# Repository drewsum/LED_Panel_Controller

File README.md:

# LED_Panel_Controller
Controls a single 64x64 HUB75E LED Panel

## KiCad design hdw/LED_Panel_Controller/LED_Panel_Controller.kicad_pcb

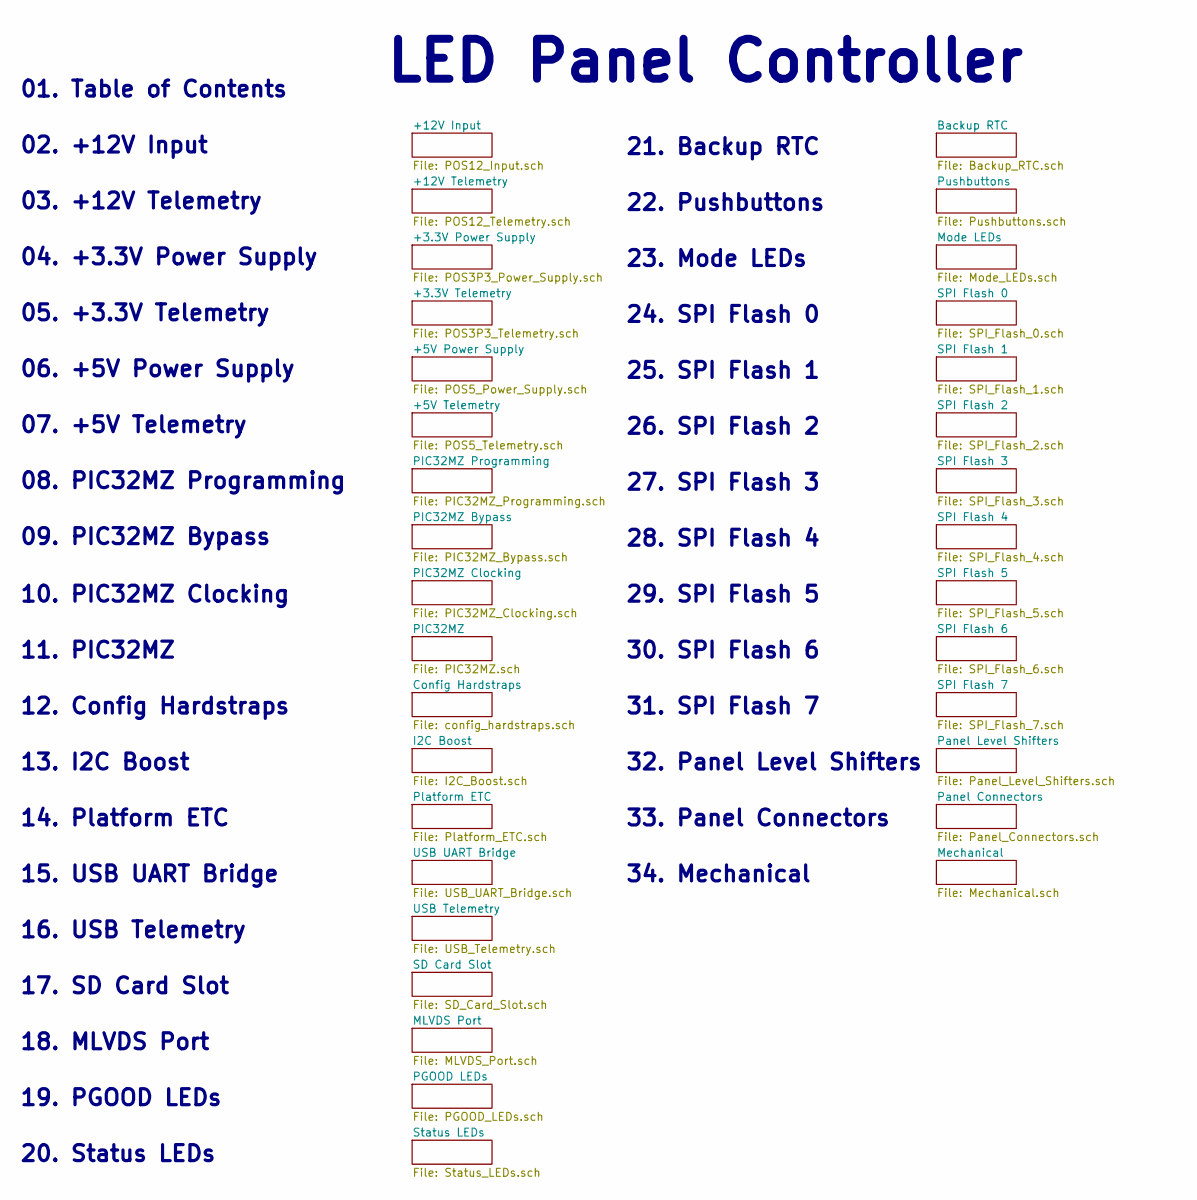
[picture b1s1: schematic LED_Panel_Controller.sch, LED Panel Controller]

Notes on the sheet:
LED Panel Controller
02. +12V Input
03. +12V Telemetry
04. +3.3V Power Supply
05. +3.3V Telemetry
06. +5V Power Supply
07. +5V Telemetry
08. PIC32MZ Programming
09. PIC32MZ Bypass
10. PIC32MZ Clocking
11. PIC32MZ
12. Config Hardstraps
13. I2C Boost
14. Platform ETC
15. USB UART Bridge
17. SD Card Slot
18. MLVDS Port
19. PGOOD LEDs
20. Status LEDs
21. Backup RTC
01. Table of Contents
22. Pushbuttons
23. Mode LEDs
24. SPI Flash 0
25. SPI Flash 1
26. SPI Flash 2
27. SPI Flash 3
28. SPI Flash 4
29. SPI Flash 5
30. SPI Flash 6
31. SPI Flash 7
32. Panel Level Shifters
33. Panel Connectors
34. Mechanical
16. USB Telemetry

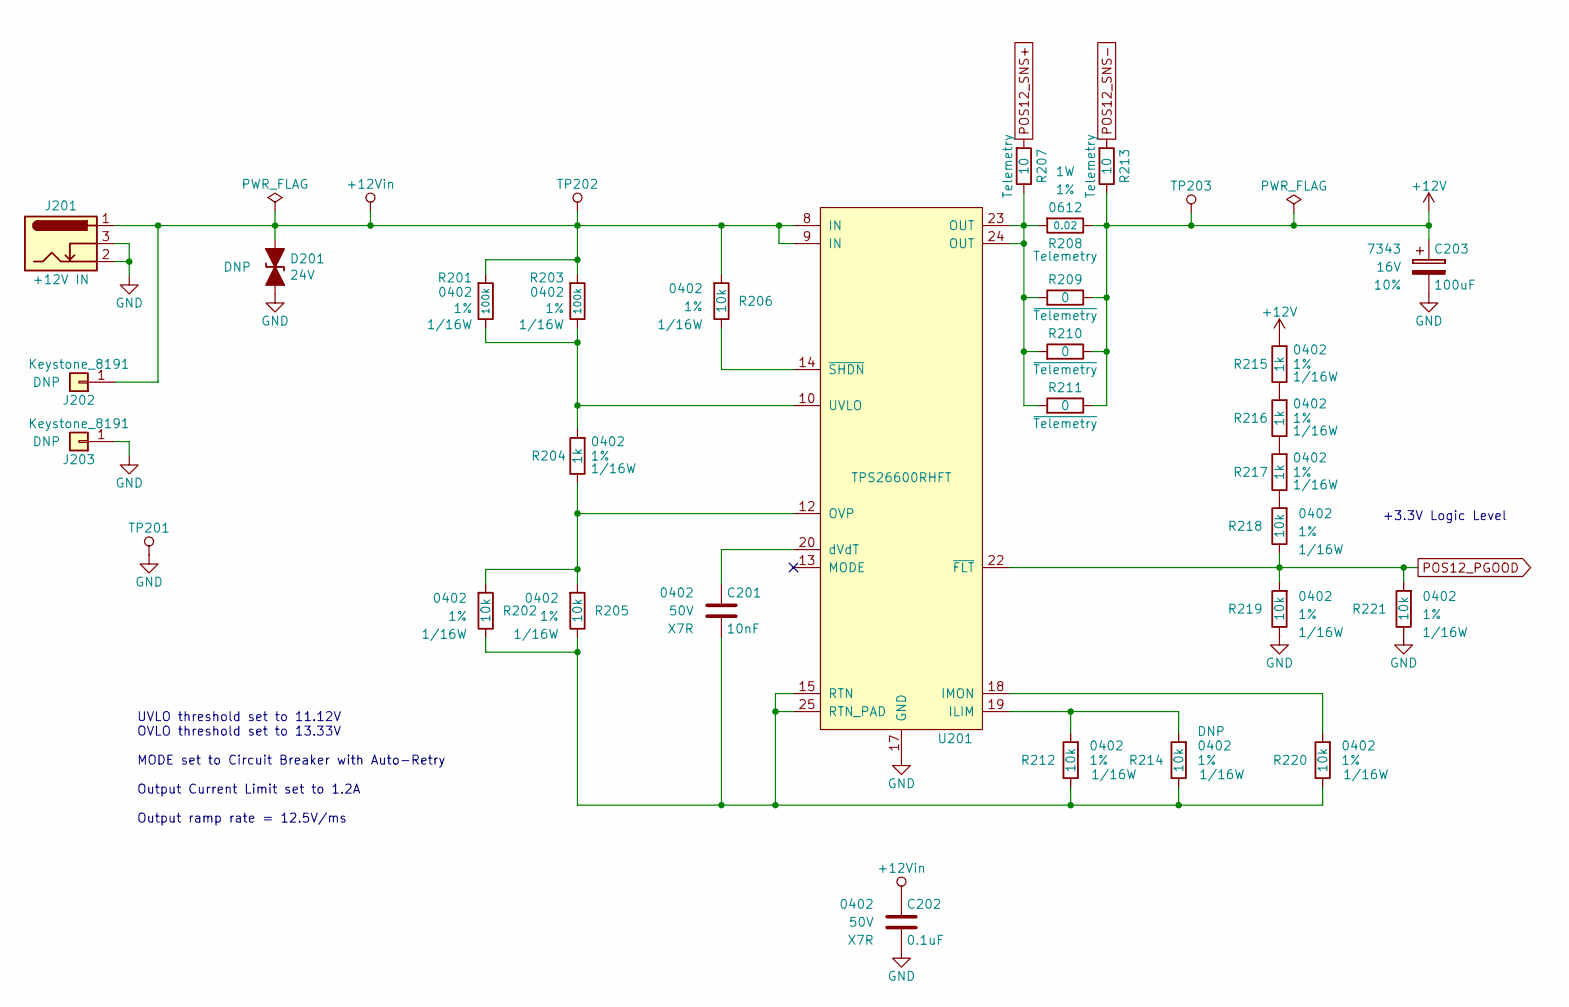
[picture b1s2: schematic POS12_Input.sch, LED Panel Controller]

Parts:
C201: 10nF; C_0402; Voltage 50V; Digi-Key PN 399-3066-1-ND
C202: 0.1uF; C_0402; Voltage 50V; Digi-Key PN 490-10698-1-ND
C203: 100uF; CP_Tantalum_Case-X_EIA-7343-43_Reflow; Voltage 16V; Tolerance 10%; Digi-Key PN 718-1102-1-ND
D201: 24V; D_SMA; Digi-Key PN SMAJ24CALFCT-ND
J201: +12V IN; BARREL_JACK
J202, J203: Keystone_8191; Digi-Key PN 36-8191-ND
R201, R203: 100k; R_0402; Tolerance 1%; Digi-Key PN RMCF0402FT100KCT-ND
R202, R205, R206, R212, R214, R218, R219, R220, R221: 10k; R_0402; Tolerance 1%; Digi-Key PN RMCF0402FT10K0CT-ND
R204, R215, R216, R217: 1k; R_0402; Tolerance 1%; Digi-Key PN RMCF0402FT1K00CT-ND
R207, R213: 10; R_0402; Tolerance 1%; Digi-Key PN RMCF0402FT10R0CT-ND
R208: 0.02; R_0612; Tolerance 1%; Digi-Key PN P16010CT-ND
R209, R210, R211: 0; R_0402; Tolerance 1%; Digi-Key PN RMCF0402ZT0R00CT-ND
TP201: TP; Pin_Header_Angled_1x01_Pitch2.54mm
TP202, TP203: TP; Test_Point
U201: TPS26600RHFT; QFN-24-1EP_4x5mm_Pitch0.5mm; Digi-Key PN 296-45478-1-ND

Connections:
+12V: C203.1, R208.2, R209.2, R210.2, R211.2, R213.2, R215.1, TP203.1; also elsewhere on the board
+12Vin: C202.1, D201.1 (A1), J201.1, J202.1, R201.1, R203.1, R206.1, TP202.1, U201.8 (IN), U201.9 (IN)
unnamed: C201.1, U201.20 (dVdT)
unnamed: C201.2, R202.2, R205.2, R212.2, R214.2, R220.2, U201.15 (RTN), U201.25 (RTN_PAD)
unnamed: R201.2, R203.2, R204.1, U201.10 (UVLO)
unnamed: R202.1, R204.2, R205.1, U201.12 (OVP)
unnamed: R206.2, U201.14 (~SHDN)
unnamed: R207.2, R208.1, R209.1, R210.1, R211.1, U201.23 (OUT), U201.24 (OUT)
unnamed: R212.1, R214.1, U201.19 (ILIM)
unnamed: R215.2, R216.1
unnamed: R216.2, R217.1
unnamed: R217.2, R218.1
unnamed: R220.1, U201.18 (IMON)
POS12_PGOOD: R218.2, R219.1, R221.1, U201.22 (~FLT); also elsewhere on the board
POS12_SNS+: R207.1; also elsewhere on the board
POS12_SNS-: R213.1; also elsewhere on the board

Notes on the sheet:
UVLO threshold set to 11.12V OVLO threshold set to 13.33V MODE set to Circuit Breaker with Auto-Retry Output Current Limit set to 1.2A Output ramp rate = 12.5V/ms
+3.3V Logic Level

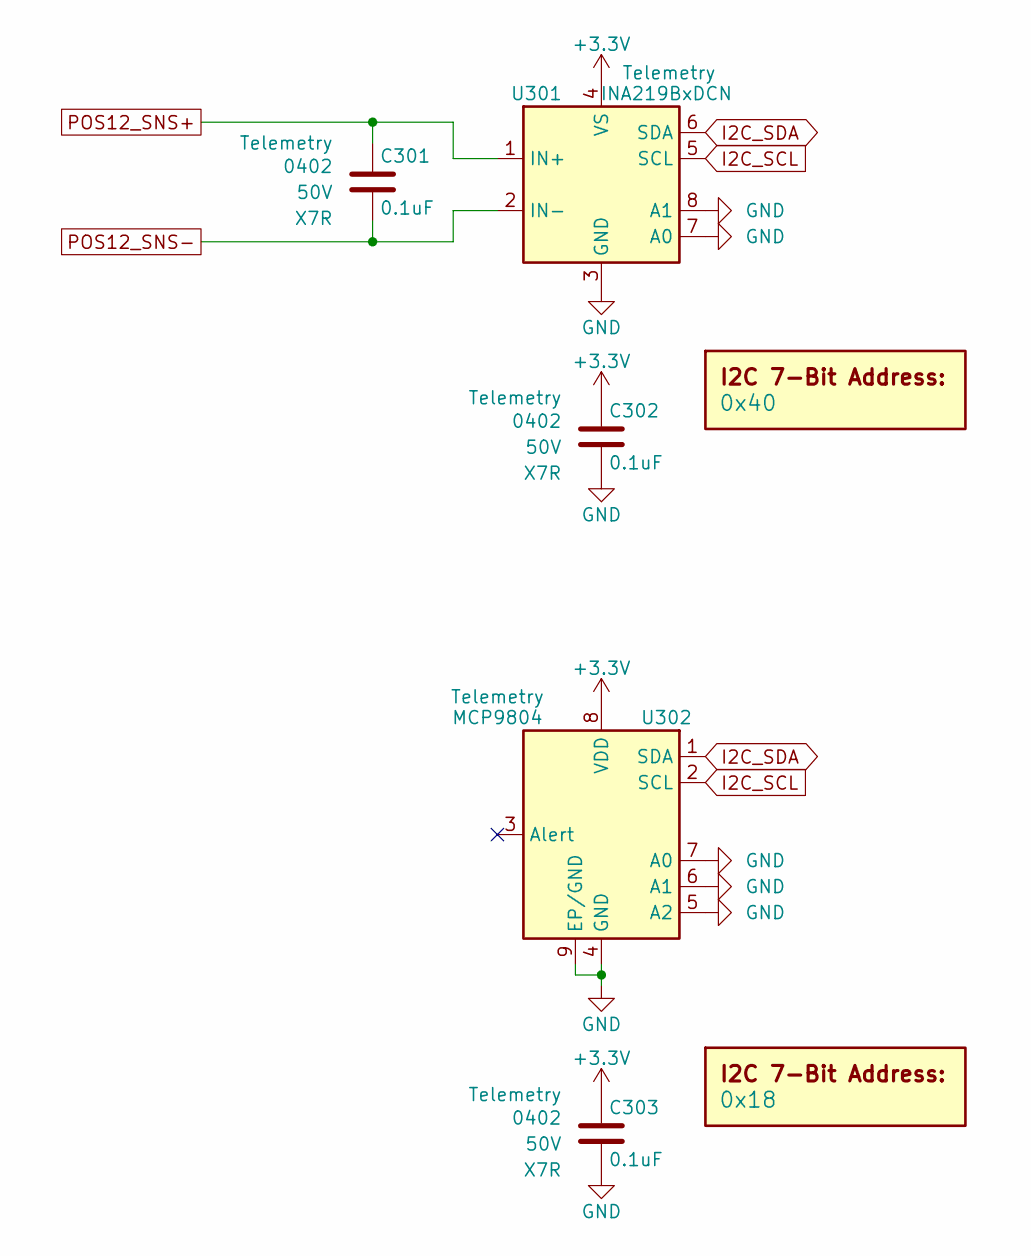
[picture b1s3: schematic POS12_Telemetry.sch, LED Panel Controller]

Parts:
C301, C302, C303: 0.1uF; C_0402; Voltage 50V; Digi-Key PN 490-10698-1-ND
DOC301: 0x40
DOC302: 0x18
U301: INA219BxDCN; SOT-23-8; Digi-Key PN 296-46420-1-ND
U302: MCP9804; DFN-8-1EP_3x2mm_P0.5mm_EP1.3x1.5mm; Digi-Key PN MCP9804T-E/MCCT-ND

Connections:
I2C_SCL: U301.5 (SCL), U302.2 (SCL); also elsewhere on the board
I2C_SDA: U301.6 (SDA), U302.1 (SDA); also elsewhere on the board
POS12_SNS+: C301.1, U301.1 (IN+); also elsewhere on the board
POS12_SNS-: C301.2, U301.2 (IN-); also elsewhere on the board

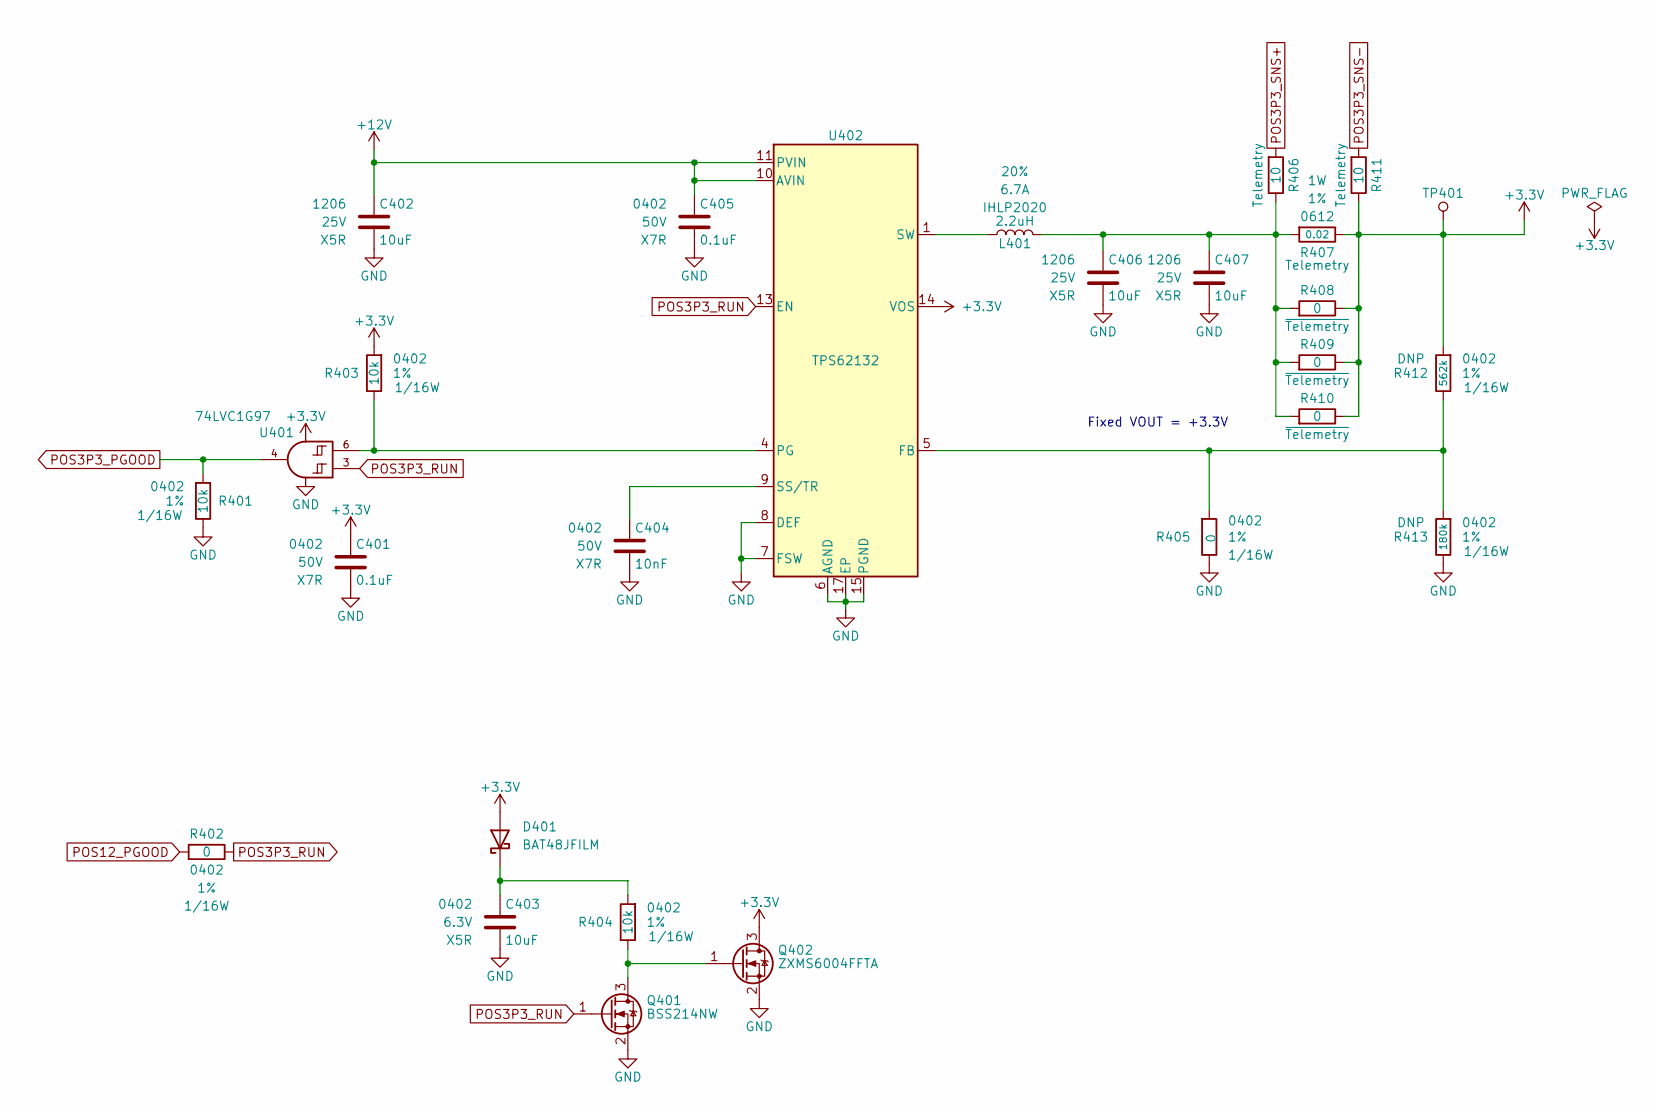
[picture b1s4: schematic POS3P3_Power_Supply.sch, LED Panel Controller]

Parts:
C401, C405: 0.1uF; C_0402; Voltage 50V; Digi-Key PN 490-10698-1-ND
C402, C406, C407: 10uF; C_1206; Voltage 25V; Digi-Key PN 399-8153-1-ND
C403: 10uF; C_0402; Voltage 6.3V; Digi-Key PN 1276-1451-1-ND
C404: 10nF; C_0402; Voltage 50V; Digi-Key PN 399-3066-1-ND
D401: BAT48JFILM; D_SOD-323; Digi-Key PN 497-5711-1-ND
L401: 2.2uH; L_Vishay_IHLP-2020; Tolerance 20%; Digi-Key PN 541-1236-1-ND
Q401: BSS214NW; SOT-323_SC-70; Digi-Key PN BSS214NWH6327XTSA1CT-ND
Q402: ZXMS6004FFTA; SOT-23; Digi-Key PN ZXMS6004FFCT-ND
R401, R403, R404: 10k; R_0402; Tolerance 1%; Digi-Key PN RMCF0402FT10K0CT-ND
R402, R405, R408, R409, R410: 0; R_0402; Tolerance 1%; Digi-Key PN RMCF0402ZT0R00CT-ND
R406, R411: 10; R_0402; Tolerance 1%; Digi-Key PN RMCF0402FT10R0CT-ND
R407: 0.02; R_0612; Tolerance 1%; Digi-Key PN P16010CT-ND
R412: 562k; R_0402; Tolerance 1%; Digi-Key PN RMCF0402FT562KCT-ND
R413: 180k; R_0402; Tolerance 1%; Digi-Key PN RMCF0402FT180KCT-ND
TP401: TP; Test_Point
U401: 74LVC1G97; SOT-363_SC-70-6; Digi-Key PN 1727-1772-1-ND
U402: TPS62132; QFN-16-1EP_3x3mm_P0.5mm_EP1.8x1.8mm; Digi-Key PN 296-29936-1-ND

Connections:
+12V: C402.1, C405.1, U402.10 (AVIN), U402.11 (PVIN), U402.12 (PVIN); also elsewhere on the board
unnamed: C403.1, D401.1 (K), R404.1
unnamed: C404.1, U402.9 (SS/TR)
unnamed: C406.1, C407.1, L401.2, R406.2, R407.1, R408.1, R409.1, R410.1
unnamed: L401.1, U402.1 (SW), U402.2 (SW), U402.3 (SW)
unnamed: Q401.3 (D), Q402.1 (G), R404.2
unnamed: R403.2, U401.6, U402.4 (PG)
unnamed: R405.1, R412.2, R413.1, U402.5 (FB)
POS3P3_PGOOD: R401.1, U401.4; also elsewhere on the board
POS3P3_RUN: Q401.1 (G), R402.2, U401.3, U402.13 (EN)
POS3P3_SNS+: R406.1; also elsewhere on the board
POS3P3_SNS-: R411.1; also elsewhere on the board
POS12_PGOOD: R402.1; also elsewhere on the board

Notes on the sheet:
Fixed VOUT = +3.3V

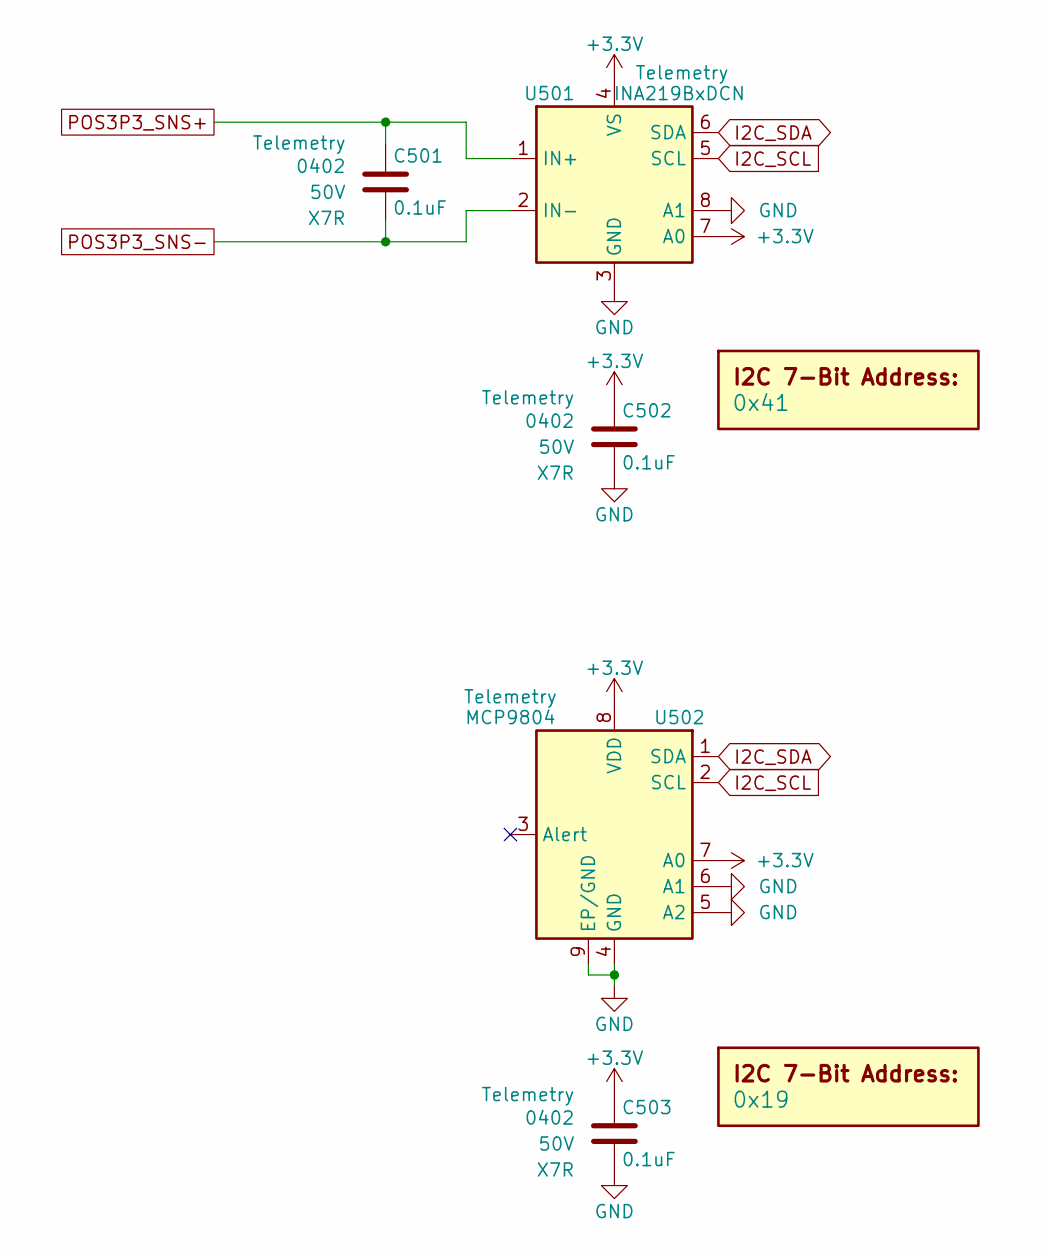
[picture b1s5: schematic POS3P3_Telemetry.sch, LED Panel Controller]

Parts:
C501, C502, C503: 0.1uF; C_0402; Voltage 50V; Digi-Key PN 490-10698-1-ND
DOC501: 0x41
DOC502: 0x19
U501: INA219BxDCN; SOT-23-8; Digi-Key PN 296-46420-1-ND
U502: MCP9804; DFN-8-1EP_3x2mm_P0.5mm_EP1.3x1.5mm; Digi-Key PN MCP9804T-E/MCCT-ND

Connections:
I2C_SCL: U501.5 (SCL), U502.2 (SCL); also elsewhere on the board
I2C_SDA: U501.6 (SDA), U502.1 (SDA); also elsewhere on the board
POS3P3_SNS+: C501.1, U501.1 (IN+); also elsewhere on the board
POS3P3_SNS-: C501.2, U501.2 (IN-); also elsewhere on the board

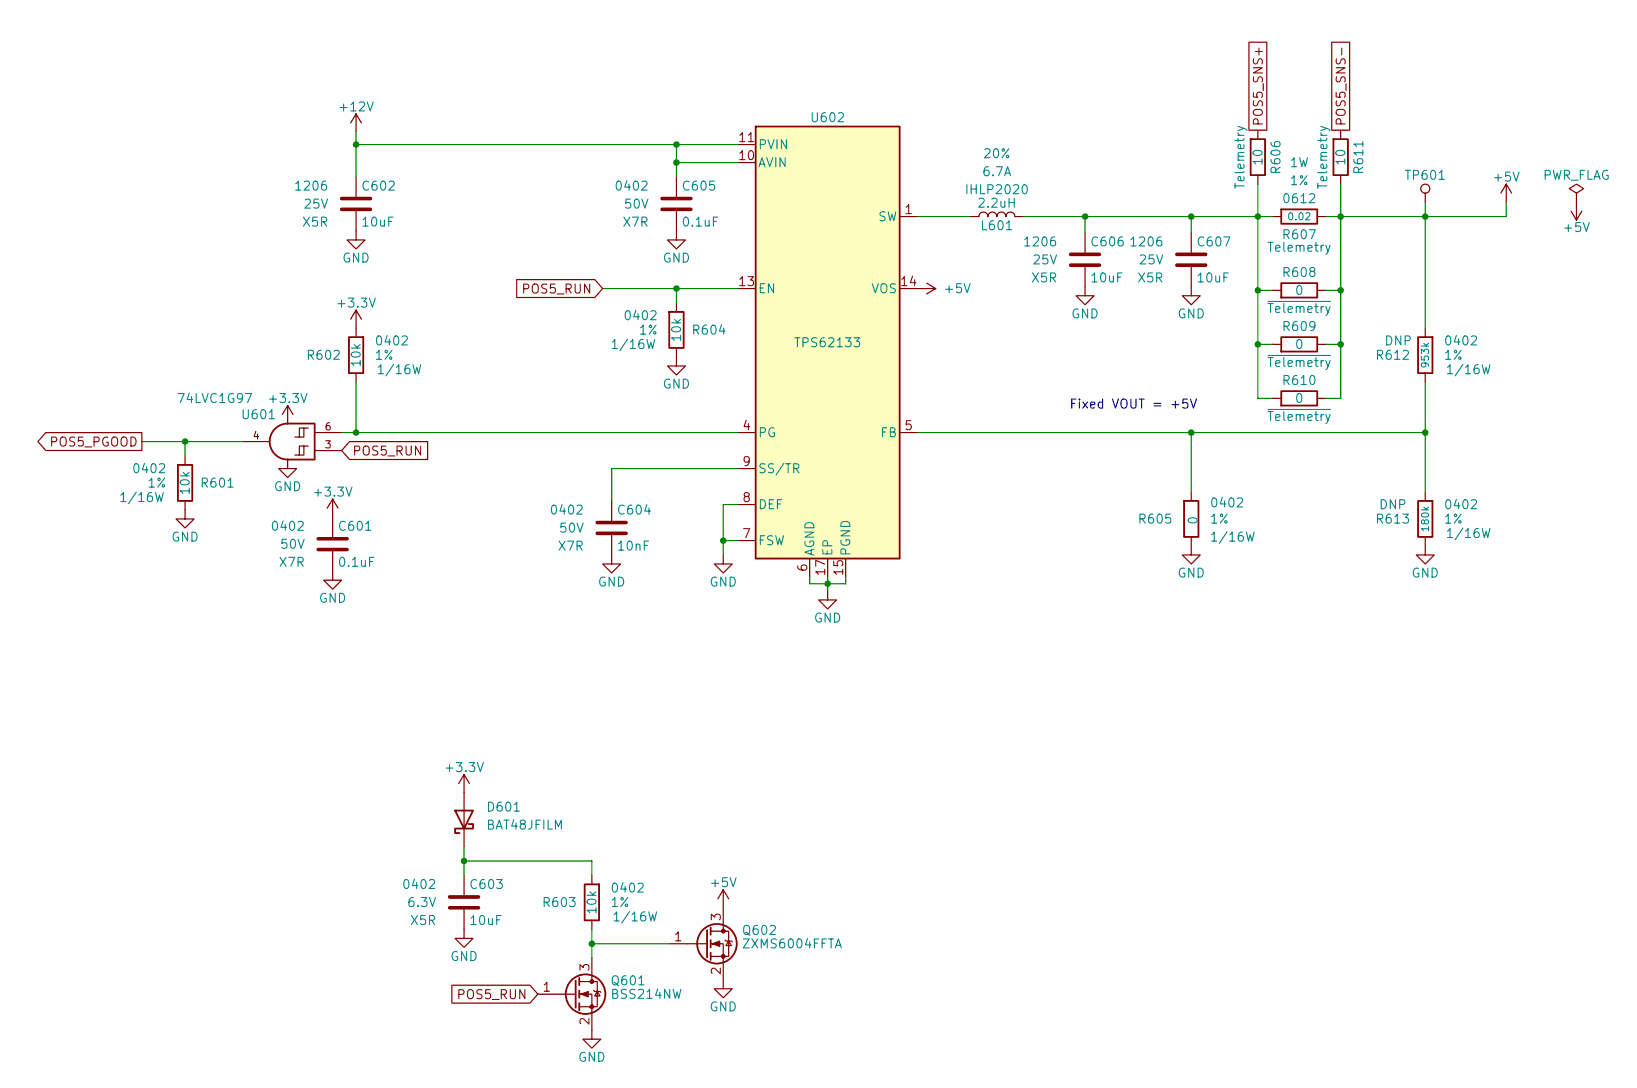
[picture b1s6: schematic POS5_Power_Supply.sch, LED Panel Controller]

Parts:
C601, C605: 0.1uF; C_0402; Voltage 50V; Digi-Key PN 490-10698-1-ND
C602, C606, C607: 10uF; C_1206; Voltage 25V; Digi-Key PN 399-8153-1-ND
C603: 10uF; C_0402; Voltage 6.3V; Digi-Key PN 1276-1451-1-ND
C604: 10nF; C_0402; Voltage 50V; Digi-Key PN 399-3066-1-ND
D601: BAT48JFILM; D_SOD-323; Digi-Key PN 497-5711-1-ND
L601: 2.2uH; L_Vishay_IHLP-2020; Tolerance 20%; Digi-Key PN 541-1236-1-ND
Q601: BSS214NW; SOT-323_SC-70; Digi-Key PN BSS214NWH6327XTSA1CT-ND
Q602: ZXMS6004FFTA; SOT-23; Digi-Key PN ZXMS6004FFCT-ND
R601, R602, R603, R604: 10k; R_0402; Tolerance 1%; Digi-Key PN RMCF0402FT10K0CT-ND
R605, R608, R609, R610: 0; R_0402; Tolerance 1%; Digi-Key PN RMCF0402ZT0R00CT-ND
R606, R611: 10; R_0402; Tolerance 1%; Digi-Key PN RMCF0402FT10R0CT-ND
R607: 0.02; R_0612; Tolerance 1%; Digi-Key PN P16010CT-ND
R612: 953k; R_0402; Tolerance 1%; Digi-Key PN RMCF0402FT953KCT-ND
R613: 180k; R_0402; Tolerance 1%; Digi-Key PN RMCF0402FT180KCT-ND
TP601: TP; Test_Point
U601: 74LVC1G97; SOT-363_SC-70-6; Digi-Key PN 1727-1772-1-ND
U602: TPS62133; QFN-16-1EP_3x3mm_P0.5mm_EP1.8x1.8mm; Digi-Key PN 296-30225-1-ND

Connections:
+5V: Q602.3 (D), R607.2, R608.2, R609.2, R610.2, R611.2, R612.1, TP601.1, U602.14 (VOS); also elsewhere on the board
+12V: C602.1, C605.1, U602.10 (AVIN), U602.11 (PVIN), U602.12 (PVIN); also elsewhere on the board
unnamed: C603.1, D601.1 (K), R603.1
unnamed: C604.1, U602.9 (SS/TR)
unnamed: C606.1, C607.1, L601.2, R606.2, R607.1, R608.1, R609.1, R610.1
unnamed: L601.1, U602.1 (SW), U602.2 (SW), U602.3 (SW)
unnamed: Q601.3 (D), Q602.1 (G), R603.2
unnamed: R602.2, U601.6, U602.4 (PG)
unnamed: R605.1, R612.2, R613.1, U602.5 (FB)
POS5_PGOOD: R601.1, U601.4; also elsewhere on the board
POS5_RUN: Q601.1 (G), R604.1, U601.3, U602.13 (EN); also elsewhere on the board
POS5_SNS+: R606.1; also elsewhere on the board
POS5_SNS-: R611.1; also elsewhere on the board

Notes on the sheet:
Fixed VOUT = +5V

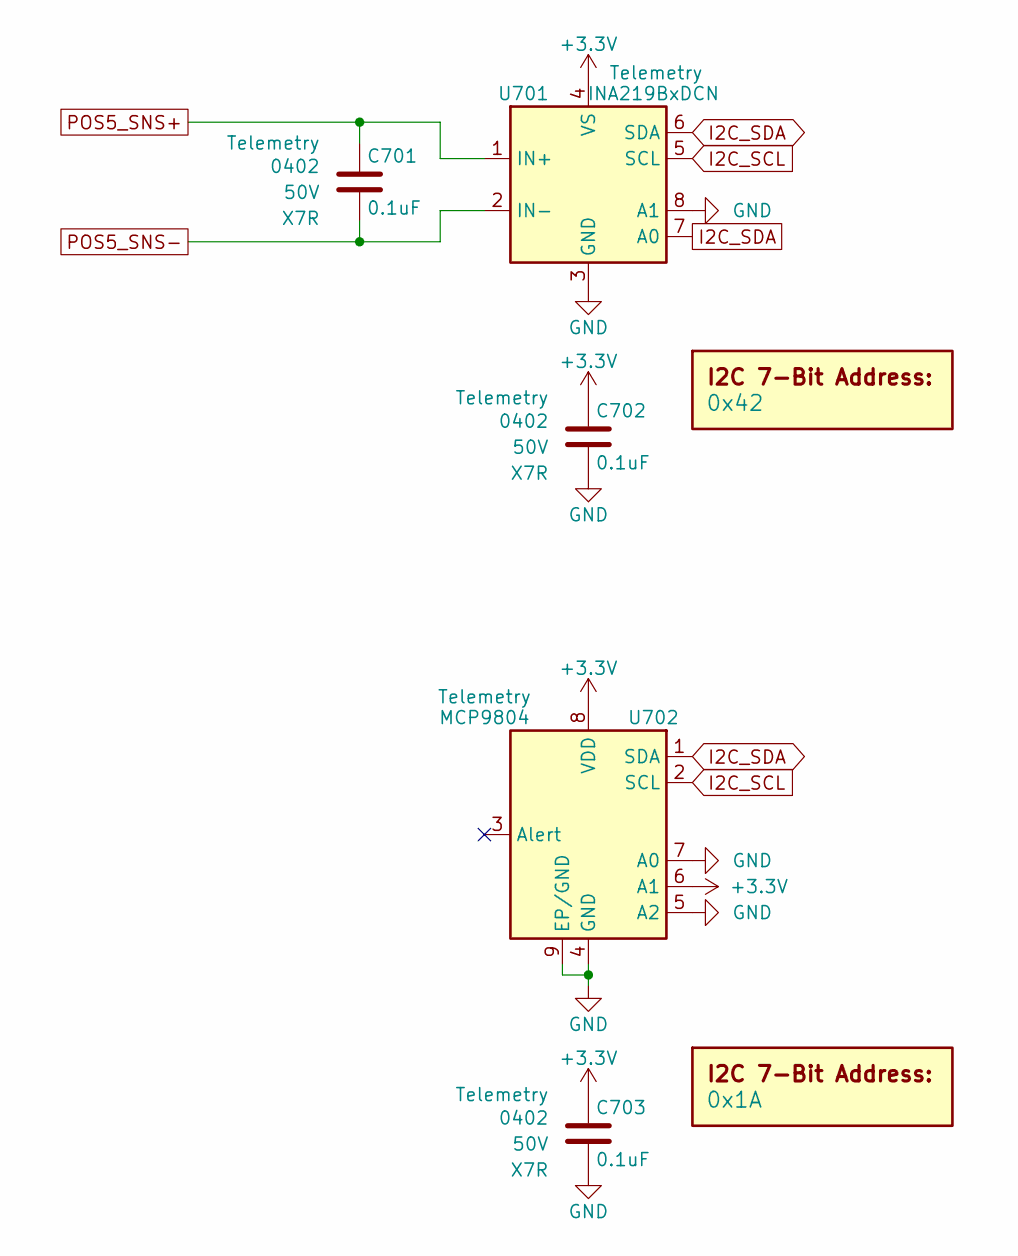
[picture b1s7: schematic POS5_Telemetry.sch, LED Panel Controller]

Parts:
C701, C702, C703: 0.1uF; C_0402; Voltage 50V; Digi-Key PN 490-10698-1-ND
DOC701: 0x42
DOC702: 0x1A
U701: INA219BxDCN; SOT-23-8; Digi-Key PN 296-46420-1-ND
U702: MCP9804; DFN-8-1EP_3x2mm_P0.5mm_EP1.3x1.5mm; Digi-Key PN MCP9804T-E/MCCT-ND

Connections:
I2C_SCL: U701.5 (SCL), U702.2 (SCL); also elsewhere on the board
I2C_SDA: U701.6 (SDA), U701.7 (A0), U702.1 (SDA); also elsewhere on the board
POS5_SNS+: C701.1, U701.1 (IN+); also elsewhere on the board
POS5_SNS-: C701.2, U701.2 (IN-); also elsewhere on the board

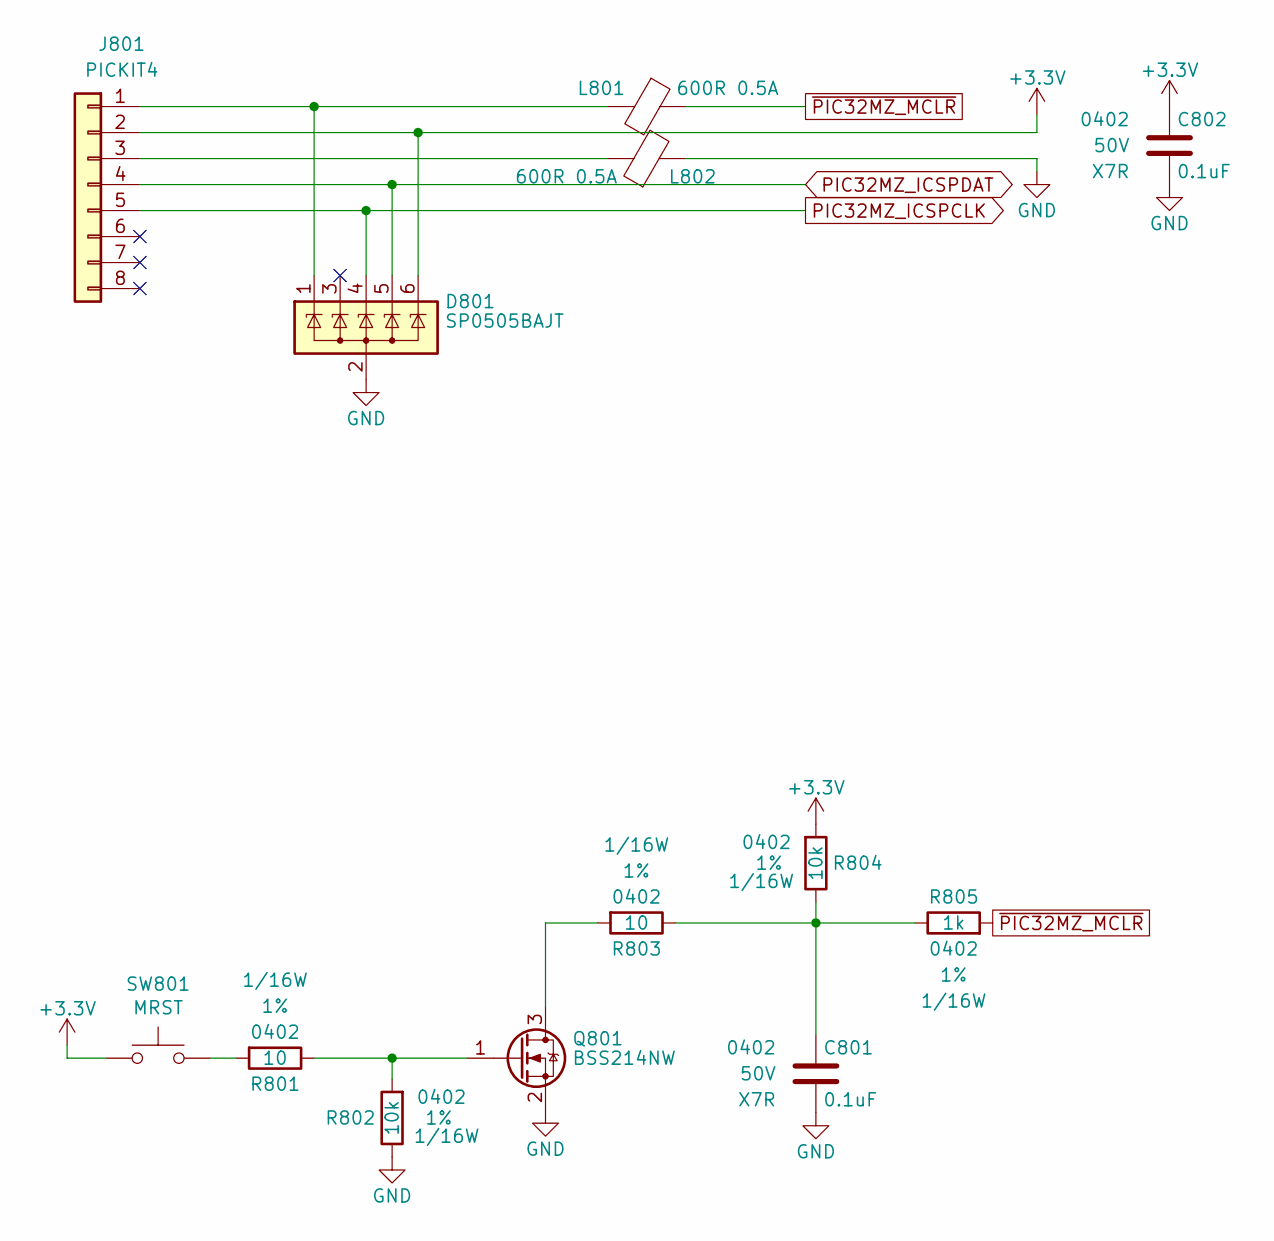
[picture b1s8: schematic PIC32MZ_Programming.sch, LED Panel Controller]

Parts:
C801, C802: 0.1uF; C_0402; Voltage 50V; Digi-Key PN 490-10698-1-ND
D801: SP0505BAJT; SOT-363_SC-70-6; Digi-Key PN F3160CT-ND
J801: PICKIT4; PICKIT4_Header
L801, L802: 600R 0.5A; L_0402; Digi-Key PN 490-5441-1-ND
Q801: BSS214NW; SOT-323_SC-70; Digi-Key PN BSS214NWH6327XTSA1CT-ND
R801, R803: 10; R_0402; Tolerance 1%; Digi-Key PN RMCF0402FT10R0CT-ND
R802, R804: 10k; R_0402; Tolerance 1%; Digi-Key PN RMCF0402FT10K0CT-ND
R805: 1k; R_0402; Tolerance 1%; Digi-Key PN RMCF0402FT1K00CT-ND
SW801: MRST; SW_PUSH_6mm

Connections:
unnamed: C801.1, R803.2, R804.2, R805.2
unnamed: D801.1 (K), J801.1, L801.2
unnamed: J801.3, L802.1
unnamed: Q801.1 (G), R801.2, R802.1
unnamed: Q801.3 (D), R803.1
unnamed: R801.1, SW801.2
PIC32MZ_ICSPCLK: D801.4 (K), J801.5; also elsewhere on the board
PIC32MZ_ICSPDAT: D801.5 (K), J801.4; also elsewhere on the board
~PIC32MZ_MCLR: L801.1, R805.1; also elsewhere on the board

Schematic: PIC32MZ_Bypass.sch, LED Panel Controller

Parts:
C901, C902, C905, C907, C909, C910, C913, C915: 0.1uF; C_0402; Voltage 50V; Digi-Key PN 490-10698-1-ND
C903, C904, C906, C908, C911, C912, C914, C916: 10uF; C_0402; Voltage 6.3V; Digi-Key PN 1276-1451-1-ND
L901, L902: 600R 0.5A; L_0402; Digi-Key PN 490-5441-1-ND

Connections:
+3.3VA_MZ: C910.1, C912.1, L901.1; also elsewhere on the board
GNDA_MZ: C910.2, C912.2, L902.1; also elsewhere on the board

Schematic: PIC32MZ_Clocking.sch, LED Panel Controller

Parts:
C1001, C1002, C1003: 0.1uF; C_0402; Voltage 50V; Digi-Key PN 490-10698-1-ND
C1004, C1005: 10uF; C_0402; Voltage 6.3V; Digi-Key PN 1276-1451-1-ND
L1001, L1002: 600R 0.5A; L_0402; Digi-Key PN 490-5441-1-ND
R1001, R1002, R1005, R1006: 10k; R_0402; Tolerance 1%; Digi-Key PN RMCF0402FT10K0CT-ND
R1003, R1004: 10; R_0402; Tolerance 1%; Digi-Key PN RMCF0402FT10R0CT-ND
TP1001: TP; Test_Point
U1001: 74LVC1G97; SOT-363_SC-70-6; Digi-Key PN 1727-1772-1-ND
X1001: ASE-8.000MHz; Oscillator_SMD_Abracon_ASE-4Pin_3.2x2.5mm; Digi-Key PN 535-9558-1-ND
X1002: ECS-327KE; Digi-Key PN XC1751CT-ND

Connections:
unnamed: C1002.1, C1004.1, L1001.1, X1001.4 (Vdd)
unnamed: C1003.1, C1005.1, L1002.1, X1002.4 (Vdd)
unnamed: R1003.1, X1001.3 (OUT)
unnamed: R1004.1, X1002.3 (OUT)
PIC32MZ_CLK_EN: R1002.1, U1001.4, X1001.1 (EN), X1002.1 (EN)
PIC32MZ_POSC_EC: R1003.2, R1005.1; also elsewhere on the board
PIC32MZ_REFCLK1: R1001.1, TP1001.1; also elsewhere on the board
PIC32MZ_SOSC_EC: R1004.2, R1006.1; also elsewhere on the board
POS3P3_PGOOD: U1001.1; also elsewhere on the board

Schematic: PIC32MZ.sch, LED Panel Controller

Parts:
C1101: 0.1uF; C_0402; Voltage 50V; Digi-Key PN 490-10698-1-ND
R1101, R1102: 10k; R_0402; Tolerance 1%; Digi-Key PN RMCF0402FT10K0CT-ND
R1103: 10K; R_0402; Tolerance 1%; Digi-Key PN RMCF0402FT10K0CT-ND
R1104: 0; R_0402; Tolerance 1%; Digi-Key PN RMCF0402ZT0R00CT-ND
U1101: PIC32MZ2048EFG100_IPF; TQFP-100_14x14mm_Pitch0.5mm; Digi-Key PN PIC32MZ2048EFG100-I/PF-ND
U1102: 74LVC1G97; SOT-363_SC-70-6; Digi-Key PN 1727-1772-1-ND

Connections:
+3.3VA_MZ: U1101.30 (AVDD); also elsewhere on the board
B0_POS3P3: U1101.100 (RE4/EBID4/AN18/PMD4); also elsewhere on the board
B1_POS3P3: U1101.3 (RE5/EBID5/AN17/RPE5/PMD5); also elsewhere on the board
CPU_Trap_LED: U1101.71 (RD0/EMDIO/AEMDIO/RPD0/RTCC/INT0); also elsewhere on the board
Cap_Touch_Mode: U1101.11 (RG7/EBIA4/AN13/C1INC/ECRS/RPG7/SDA4/PMA4); also elsewhere on the board
Cap_Touch_Power: U1101.10 (RG6/AN14/C1IND/ECOL/RPG6/SCK2); also elsewhere on the board
Error_LED: U1101.66 (RA14/AETXCLK/RPA14/SCL1); also elsewhere on the board
FLASH_SPI_MISO: U1101.33 (RB9/EBIA7/AN49/RPB9/PMA7); also elsewhere on the board
FLASH_SPI_MOSI: U1101.34 (RB10/EBIA13/CVREFOUT/AN5/RPB10/PMA13); also elsewhere on the board
FLASH_SPI_SCK: U1101.43 (RB14/EBIA1/AN9/ERXD2/AETXD3/RPB14/SCK3/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); also elsewhere on the board
Flash_Slideshow_Mode_LED: U1101.87 (RG1/EBID9/ETXERR/RPG1/PMD9); also elsewhere on the board
G0_POS3P3: U1101.98 (RE2/EBID2/PMD2); also elsewhere on the board
G1_POS3P3: U1101.99 (RE3/EBID3/RPE3/PMD3); also elsewhere on the board
GNDA_MZ: U1101.31 (AVSS); also elsewhere on the board
Heartbeat_LED: U1101.68 (RD9/EBIA15/RPD9/PMCS2/PMA15); also elsewhere on the board
I2C_SCL: R1102.2, U1101.65 (RF5/EBIA8/RPF5/SCL5/PMA8); also elsewhere on the board
I2C_SDA: R1101.2, U1101.64 (RF4/EBIA9/RPF4/SDA5/PMA9); also elsewhere on the board
MLVDS_SPI_MOSI: U1101.48 (RD15/AN33/AETXD1/RPD15/SCK6); also elsewhere on the board
MLVDS_SPI_SCK: U1101.69 (RD10/RPD10/SCK4); also elsewhere on the board
MLVDS_Stream_Mode_LED: U1101.32 (RB8/EBIA10/AN48/RPB8/PMA10); also elsewhere on the board
PGOOD_LED_SHDN: U1101.58 (RF8/EBIRDY2/RPF8/SCL3); also elsewhere on the board
PIC32MZ_ICSPCLK: U1101.26 (RB6/PGEC2/AN46/RPB6); also elsewhere on the board
PIC32MZ_ICSPDAT: U1101.27 (RB7/PGED2/AN47/RPB7); also elsewhere on the board
PIC32MZ_POSC_EC: U1101.49 (RC12/OSC1/CLKI); also elsewhere on the board
PIC32MZ_REFCLK1: U1101.72 (RC13/SOSCI/RPC13); also elsewhere on the board
PIC32MZ_SOSC_EC: U1101.73 (RC14/SOSCO/RPC14/T1CK); also elsewhere on the board
PIC32MZ_UART_RX_OR: R1103.2, U1101.77 (RD2/EBID14/ETXEN/RPD2/PMD14), U1102.4
POS3P3_PGOOD: U1101.40 (RF12/TDO/EBIA17/AN31/RPF12); also elsewhere on the board
POS5_PGOOD: U1101.41 (RB12/EBIA11/AN7/ERXD0/AECRS/PMA11); also elsewhere on the board
POS5_RUN: U1101.42 (RB13/AN8/ERXD1/AECOL); also elsewhere on the board
POS5_USB_PGOOD: U1101.57 (RF2/EBIRDY3/RPF2/SDA3); also elsewhere on the board
POS12_PGOOD: U1101.35 (RB11/AN6/ERXERR/AETXERR); also elsewhere on the board
Panel_CLK_POS3P3: U1101.8 (RC3/~EBIWE~/AN20/RPC3/PMWR); also elsewhere on the board
Panel_Dim_PWM: U1101.12 (RG8/EBIA3/AN12/C2IND/ERXDV/ECRSDV/AERXD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); also elsewhere on the board
Panel_LAT_POS3P3: U1101.20 (RB5/AN45/C1INA/RPB5); also elsewhere on the board
Prog1_Mode_LED: U1101.16 (RG9/EBIA2/AN11/C2INC/ERXCLK/EREFCLK/AER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); also elsewhere on the board
Prog2_Mode_LED: U1101.96 (RG12/TRD1/SQID1); also elsewhere on the board
Prog3_Mode_LED: U1101.97 (RG13/TRD0/SQID0); also elsewhere on the board
Prog4_Mode_LED: U1101.95 (RG14/TRD2/SQID2); also elsewhere on the board
R0_POS3P3: U1101.91 (RE0/EBID0/PMD0); also elsewhere on the board
R1_POS3P3: U1101.94 (RE1/EBID1/PMD1); also elsewhere on the board
RS422_UART_RX: U1102.6; also elsewhere on the board
RS422_UART_TX: R1104.2; also elsewhere on the board
Reset_LED: U1101.67 (RA15/AETXEN/RPA15/SDA1); also elsewhere on the board
Row_A_POS3P3: U1101.25 (RB0/PGED1/AN0/RPB0); also elsewhere on the board
Row_B_POS3P3: U1101.24 (RB1/PGEC1/AN1/RPB1); also elsewhere on the board
Row_C_POS3P3: U1101.23 (RB2/AN2/C2INB/RPB2); also elsewhere on the board
Row_D_POS3P3: U1101.22 (RB3/AN3/C2INA/RPB3); also elsewhere on the board
Row_E_POS3P3: U1101.21 (RB4/AN4/C1INB); also elsewhere on the board
SD_SPI_MISO: U1101.6 (RC1/EBIA6/AN22/RPC1/PMA6); also elsewhere on the board
SD_SPI_MOSI: U1101.86 (RF1/EBID10/ETXD0/RPF1/PMD10); also elsewhere on the board
SD_SPI_SCK: U1101.39 (RF13/TDI/EBIA18/AN30/RPF13/SCK5); also elsewhere on the board
USB_Stream_Mode_LED: U1101.88 (RG0/EBID8/RPG0/PMD8); also elsewhere on the board
VBAT_ADC: U1101.18 (RE8/AN25/AERXD0/RPE8); also elsewhere on the board
VBAT_PGOOD: U1101.44 (RB15/EBIA0/AN10/ERXD3/AETXD2/RPB15/OCFB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); also elsewhere on the board
Void_Mode_LED: U1101.19 (RE9/AN26/AERXD1/RPE9); also elsewhere on the board
~FLASH_SPI_CE0: U1101.17 (RA0/TMS/EBIA16/AN24); also elsewhere on the board
~FLASH_SPI_CE1: U1101.38 (RA1/TCK/EBIA19/AN29); also elsewhere on the board
~FLASH_SPI_CE2: U1101.59 (RA2/~EBICS0~/SCL2); also elsewhere on the board
~FLASH_SPI_CE3: U1101.60 (RA3/EBIRDY1/SDA2); also elsewhere on the board
~FLASH_SPI_CE4: U1101.61 (RA4/EBIA14/PMCS1/PMA14); also elsewhere on the board
~FLASH_SPI_CE5: U1101.2 (RA5/EBIA5/AN34/PMA5); also elsewhere on the board
~FLASH_SPI_CE6: U1101.89 (RA6/TRCLK/SQICLK); also elsewhere on the board
~FLASH_SPI_CE7: U1101.90 (RA7/TRD3/SQID3); also elsewhere on the board
~MODULE_RE: U1101.79 (RD12/EBID12/ETXD2/RPD12/PMD12); also elsewhere on the board
~PIC32MZ_MCLR: U1101.15 (~MCLR~); also elsewhere on the board
~Panel_OE_POS3P3: U1101.76 (RD1/RPD1/SCK1); also elsewhere on the board
~SD_CARD_DET: U1101.9 (RC4/~EBIOE~/AN19/RPC4/PMRD); also elsewhere on the board
~SD_SPI_CS: U1101.7 (RC2/EBIA12/AN21/RPC2/PMA12); also elsewhere on the board
~SPI_FLASH_Config: U1101.1 (RG15/AN23/AERXERR); also elsewhere on the board
~Telemetry_Config: U1101.85 (RF0/EBID11/ETXD1/RPF0/PMD11); also elsewhere on the board

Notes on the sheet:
SDA5
ICSP2CLK
POSC
REFCLKO1
SOSC
U1RX
U1TX
PMD0
PMD1
PMD2
PMD3
PMD4
PMD5
PMWR
ICSP2DAT
SCL5
PMD7
PMD6
DNC these two pins - unused PMP bits can't be disabled
OC3
SCK3
SDO3
SDI3
SCK4
SCK5
SDI5
SDO5
OC5
AN25
INT2
INT4
~SS4
SDI4

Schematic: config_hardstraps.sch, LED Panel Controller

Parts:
C1201: 0.1uF; C_0402; Voltage 50V; Digi-Key PN 490-10698-1-ND
DOC1201: 0x1B
J1201: PIC_UART; PinHeader_1x03_P2.54mm_Vertical
J1203: I2C; PinHeader_1x03_P2.54mm_Vertical
J1204: WIFI_SPI; PinHeader_1x04_P2.54mm_Vertical
J1205: SD_SPI; PinHeader_1x04_P2.54mm_Vertical
J1206: FLASH_SPI; PinHeader_1x04_P2.54mm_Vertical
R1201, R1203, R1205, R1207, R1209: 10k; R_0402; Tolerance 1%; Digi-Key PN RMCF0402FT10K0CT-ND
R1202, R1204, R1206, R1208, R1210: 10; R_0402; Tolerance 1%; Digi-Key PN RMCF0402FT10R0CT-ND
U1201: MCP9804; DFN-8-1EP_3x2mm_P0.5mm_EP1.3x1.5mm; Digi-Key PN MCP9804T-E/MCCT-ND

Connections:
FLASH_SPI_MISO: J1206.3; also elsewhere on the board
FLASH_SPI_MOSI: J1206.2; also elsewhere on the board
FLASH_SPI_SCK: J1206.1; also elsewhere on the board
I2C_SCL: J1203.2, U1201.2 (SCL); also elsewhere on the board
I2C_SDA: J1203.1, U1201.1 (SDA); also elsewhere on the board
MLVDS_SPI_MOSI: J1204.2; also elsewhere on the board
MLVDS_SPI_SCK: J1204.1; also elsewhere on the board
SD_SPI_MISO: J1205.3; also elsewhere on the board
SD_SPI_MOSI: J1205.2; also elsewhere on the board
SD_SPI_SCK: J1205.1; also elsewhere on the board
~MODULE_RE: J1204.3; also elsewhere on the board
~SPI_FLASH_Config: R1203.2, R1204.1; also elsewhere on the board
~Telemetry_Config: R1201.2, R1202.1; also elsewhere on the board

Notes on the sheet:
Ambient Temp Sense
